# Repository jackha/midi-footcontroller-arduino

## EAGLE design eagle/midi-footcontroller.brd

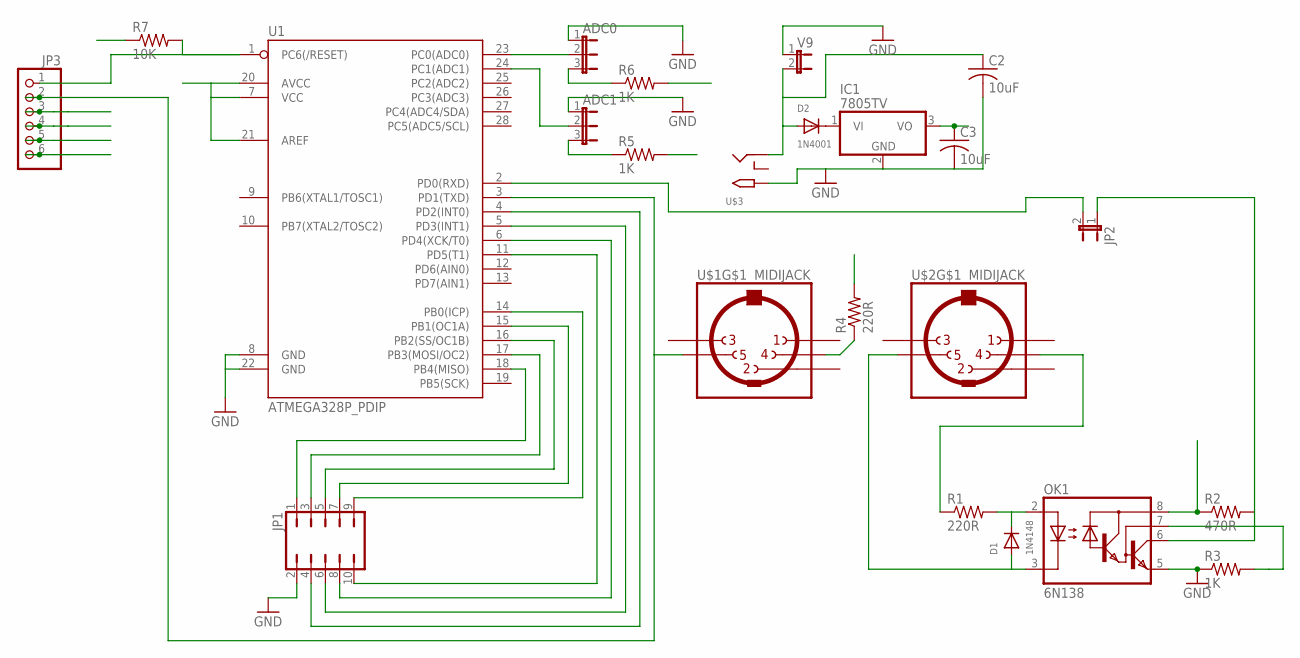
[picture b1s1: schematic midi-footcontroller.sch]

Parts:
ADC0, ADC1: JP2E; JP2
C2, C3: 10uF; C025-025X050
D1: 1N4148; DO-1N4148
D2: 1N4001; DO-1N4148
IC1: 7805TV; TO220V
JP1: JP5Q
JP2: JP1E; JP1
JP3: PINHD-1X6LOCK; 1X06-BIGLOCK
OK1: 6N138; DIL08
R1, R4: 220R; 0207/9
R2: 470R; 0207/9
R3, R5, R6: 1K; 0207/9
R7: 10K; 0207/9
U1: ATMEGA328P_PDIP; DIL28-3
U$1, U$2: MIDIJACK; CP-2350
U$3: 2.1MMJACKTHM; PJ-102A
V9: JP1E; JP1

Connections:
GND: ADC0.1, ADC1.1, C2.2, C3.2, IC1.2 (GND), JP1.2, JP3.5, OK1.5 (GND), R3.1, U1.8 (GND), U1.22 (GND), U$3.TIP, V9.1
unnamed: D1.C, OK1.2 (A), R1.2
unnamed: D1.A, OK1.3 (C), U$2.5
unnamed: R1.1, U$2.4
unnamed: D2.C, IC1.1 (VI)
unnamed: OK1.7 (VB), R3.2
unnamed: R4.1, U$1.4
unnamed: ADC0.2, U1.23 (PC0(ADC0))
unnamed: JP1.10, U1.11 (PD5(T1))
unnamed: ADC1.2, U1.24 (PC1(ADC1))
unnamed: ADC0.3, R6.1
unnamed: ADC1.3, R5.1
unnamed: JP1.8, U1.6 (PD4(XCK/T0))
unnamed: JP1.6, U1.5 (PD3(INT1))
unnamed: JP1.4, U1.4 (PD2(INT0))
unnamed: JP1.1, U1.18 (PB4(MISO))
unnamed: JP2.1, OK1.6 (VO), R2.2
unnamed: JP1.9, U1.14 (PB0(ICP))
unnamed: JP1.7, U1.15 (PB1(OC1A))
unnamed: JP1.5, U1.16 (PB2(SS/OC1B))
unnamed: JP1.3, U1.17 (PB3(MOSI/OC2))
unnamed: JP3.1, R7.2, U1.1 (PC6(/RESET))
RXD: JP2.2, JP3.3, U1.2 (PD0(RXD))
TXD: JP3.2, U1.3 (PD1(TXD)), U$1.5
V5: C3.1, IC1.3 (VO), JP3.4, OK1.8 (VCC), R2.1, R4.2, R5.2, R6.2, R7.1, U1.7 (VCC), U1.20 (AVCC), U1.21 (AREF)
V9: C2.1, D2.A, U$3.RING, V9.2

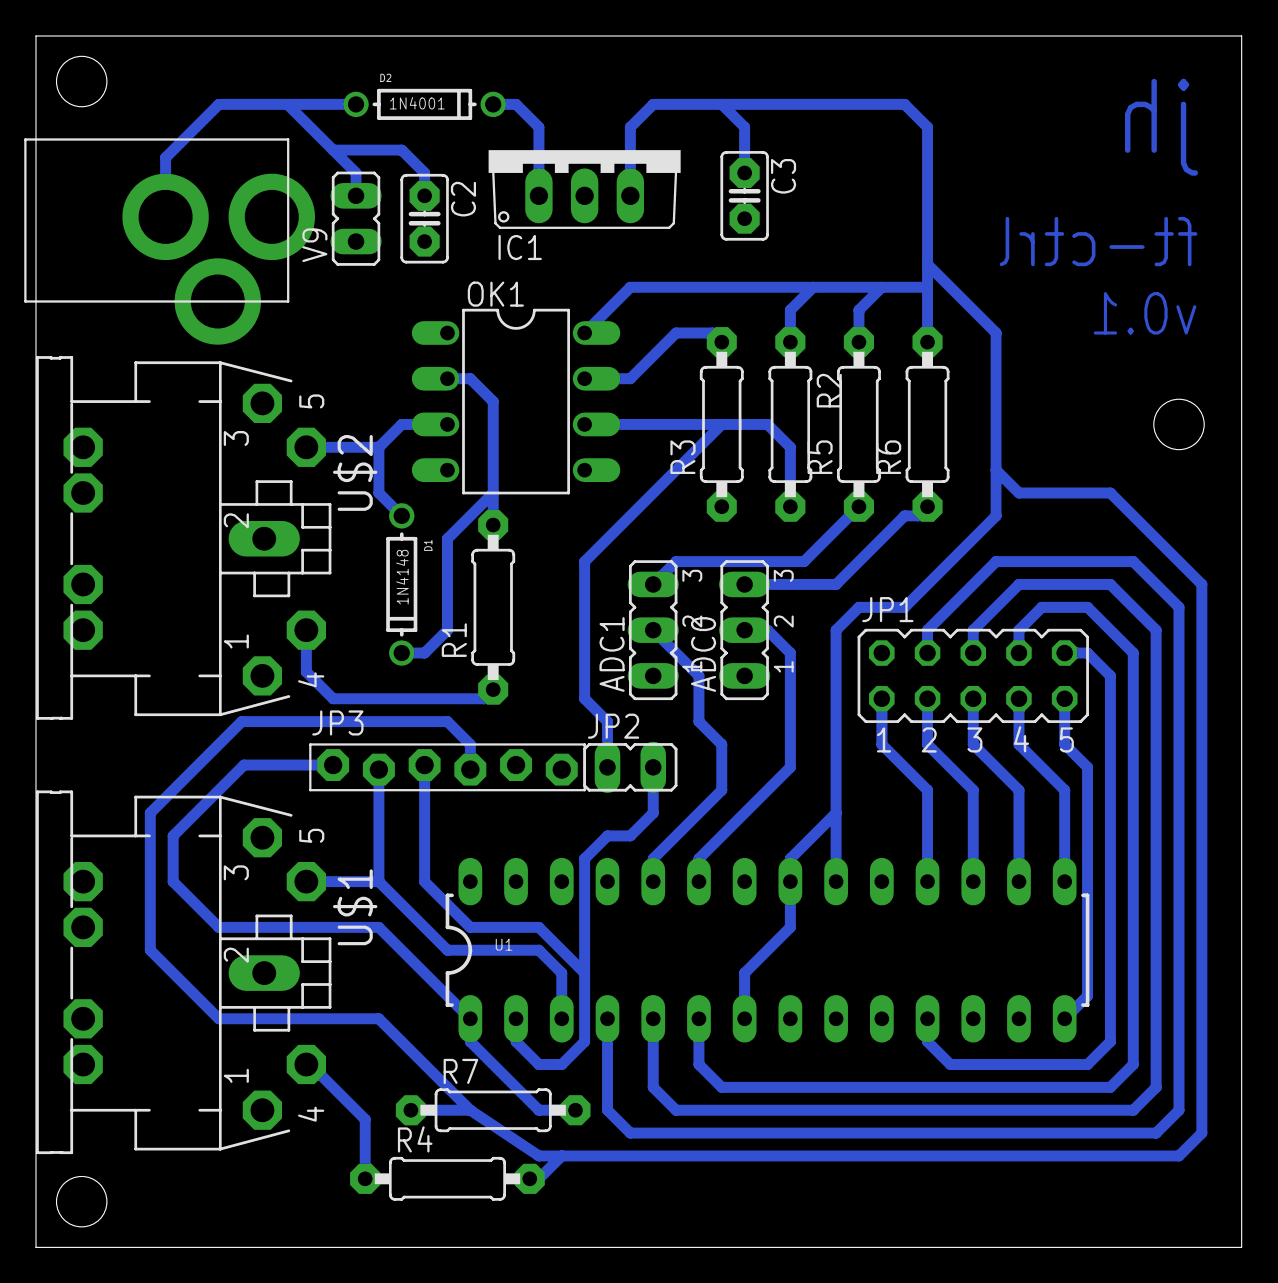
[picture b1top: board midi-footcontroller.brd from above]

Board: 2 copper layers, 67.0 x 67.3 mm, 23 parts (0 on the bottom side), 26 nets.

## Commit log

2015-11-15 readme
2015-11-15 text
2015-11-15 thingiverse
2015-11-15 testing image
2015-11-15 test
2015-11-15 image
2016-01-19 moved .ino to proper folder
2016-01-22 added eagle folder
2016-01-22 added all files

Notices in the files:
parts and their libraries:
SparkFun-DigitalIC: Licensing: Creative Commons ShareAlike 4.0 International - https://creativecommons.org/licenses/by-sa/4.0
